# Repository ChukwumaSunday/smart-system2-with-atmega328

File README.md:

# smart-system2-with-atmega328
Pro-Tracking Solution Board is an ecosystem friendly onboard tracking technology and multi-functional development board based on ATMEGA328 microcontroller, designed to meet the requirements of embedded systems, vehicles/general tracking, providing a comprehensive set of features and peripherals on a single chip. 

PRO TRACKER SYSTEM
ABSTRACT:
The research is about creating a system for tracking vehicle, driver and products. Objective of the research is to design, develop and develop a GPS based
Tracking System in order to monitor and display location of vehicle on Google Maps and Other Dashboards. This system used ATMEGA328 as a microcontroller and it will be used as the main processing unit. Next, SIM7600E 4G LTE GSM/GPS module is used for network connectivity, routing the coordinate and connecting with the user.

INTRODUCTION
	Pro-Tracker Solution Board is an ecosystem friendly onboard tracking technology and multi-functional development board based on SIM7600E module that supports 4G network and  also support 2G/3G network communications, controlled by STM32 microcontroller, designed to meet the requirements of embedded systems, vehicles/general tracking, providing a comprehensive set of features and peripherals on a single board for DIY project kits. 
	The system is optimized for low power consumption and real-time processing, making it suitable for wide rand of applications.

AIM:
	To develop a multi-fuctional system that will solve the problem of location, driver and product tracking for both the military and civilians, perform driver and vehicle control, real time monitoring and ubiquitous in developing embedded systems/IoT technologies.
	To optimize the system for low power consumption and real-time processing, making it suitable for wide rand of applications.
	  To design a system that can be used in consumer products such as Vehicle Tracking System(VTS), Appliances Remote Controls, Motor Control Systems, IoT Projects, Medical devices, Gaming Console, Home Automation Systems and more.
Achievement: 
	Done with the schematic designs, board layout and ready for PCB fabrication.
Result: 
	No test carried out yet on the system as it’s still at design stage
Status of the project: 
	First stage which is PCB development is done. Therefore, the project is 40% near completion.
Conclusion:
	 All hands are on desk to ensure the project is completed as soon as possible if all the necessary system requirements are made available.

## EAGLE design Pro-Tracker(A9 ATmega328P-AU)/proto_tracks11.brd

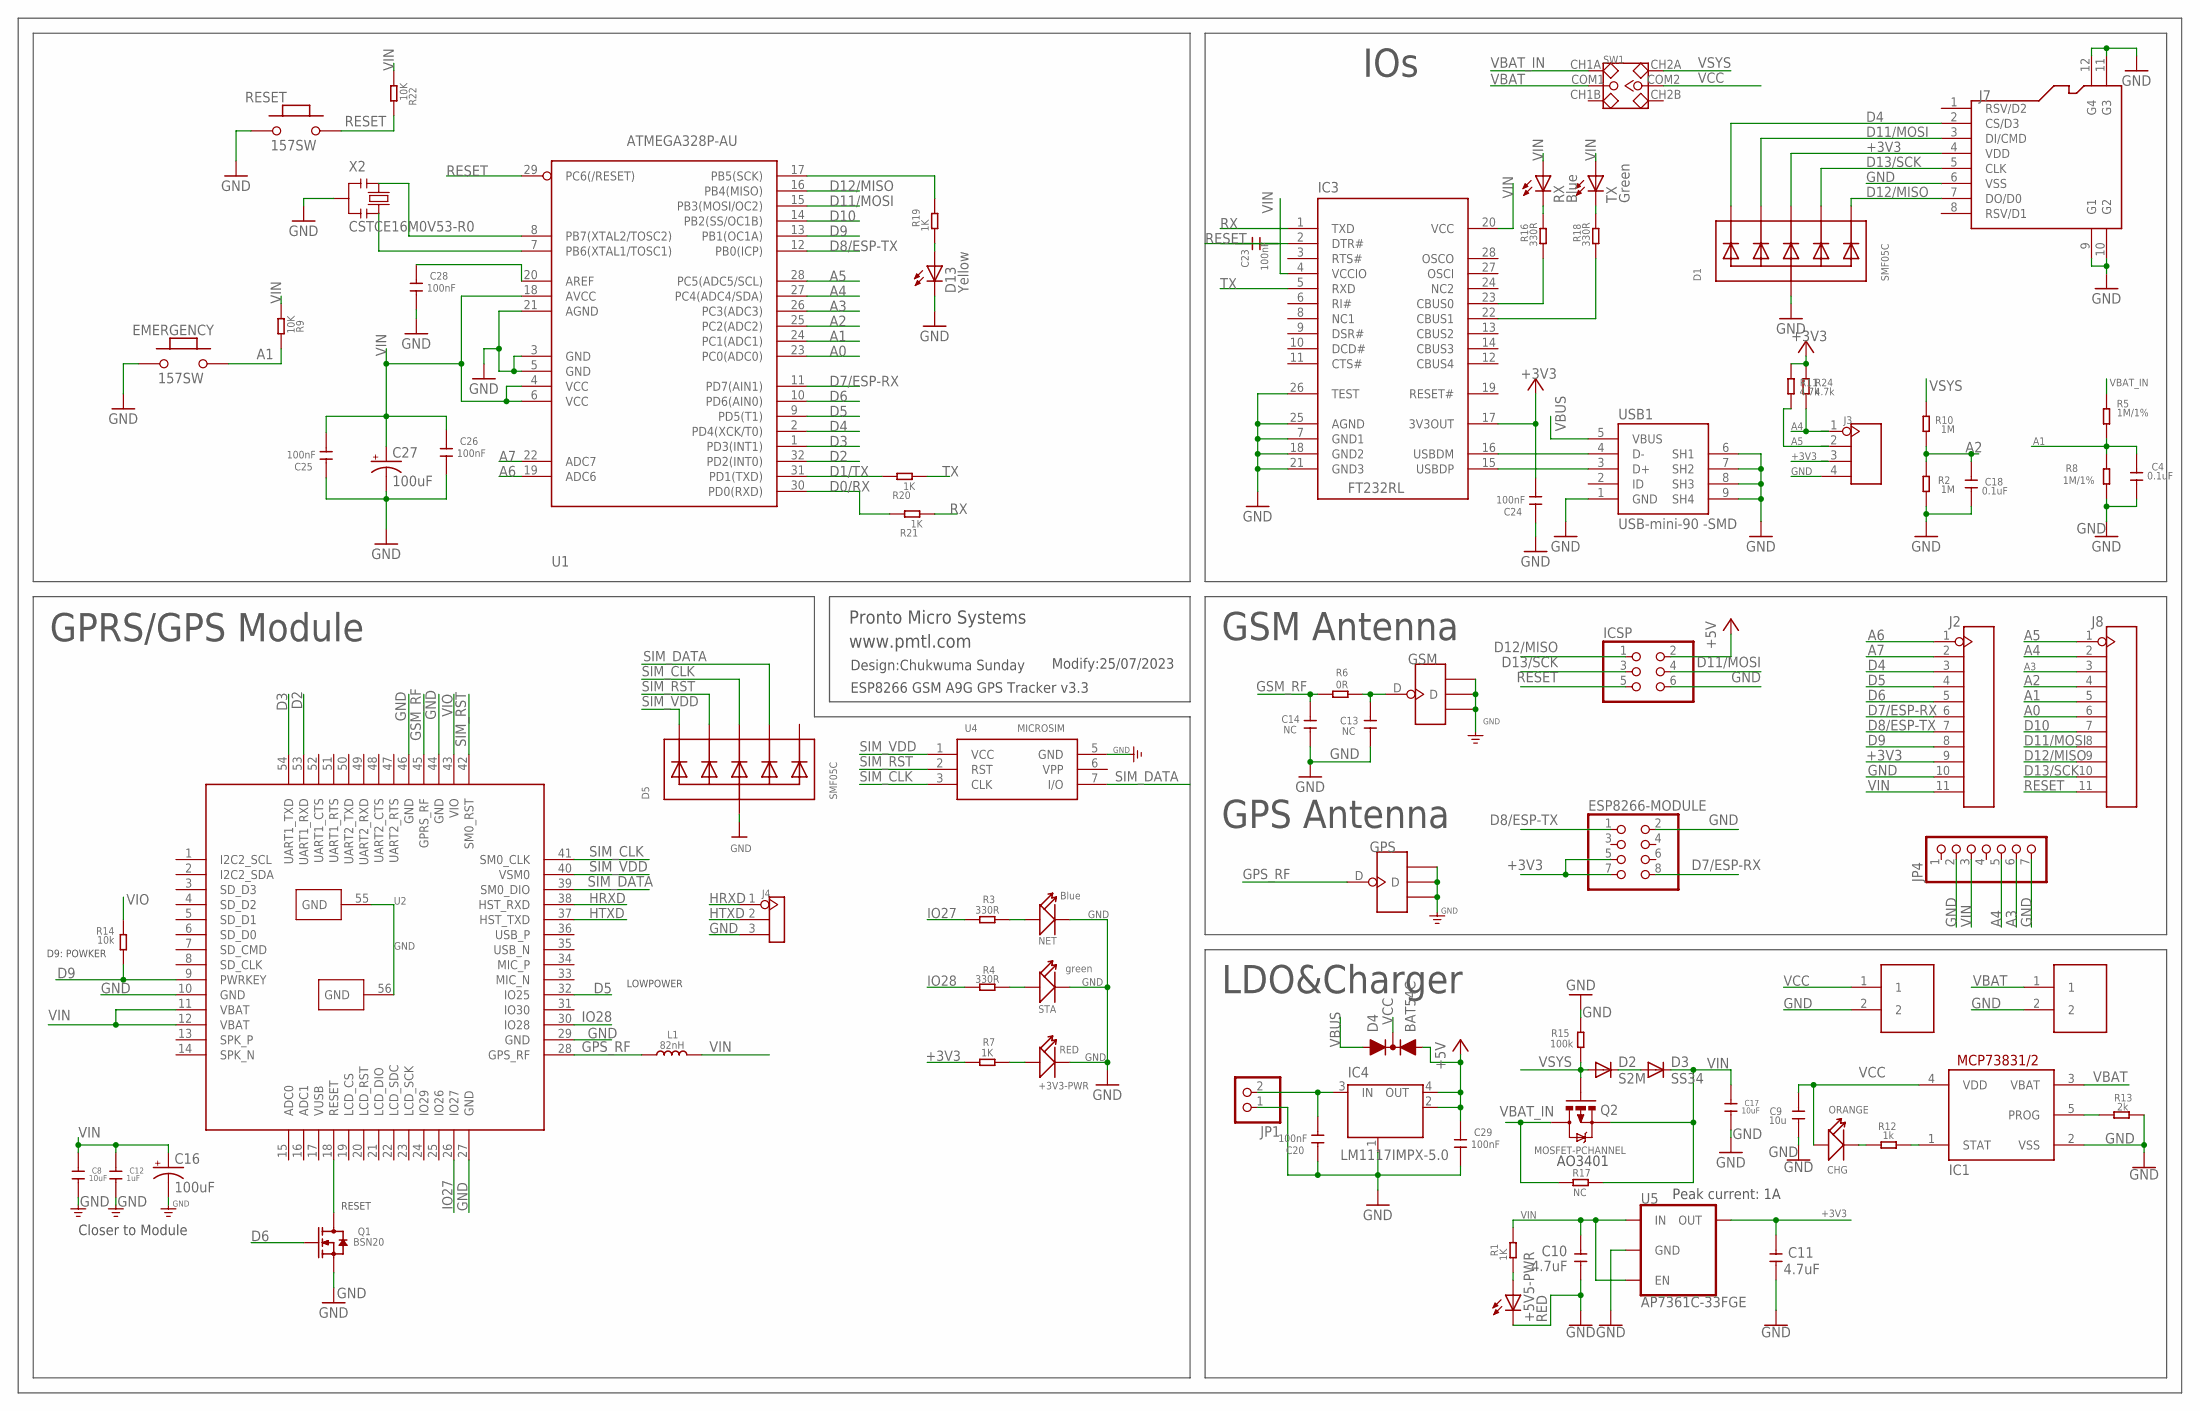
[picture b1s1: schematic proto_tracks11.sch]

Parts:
+3V3-PWR: RED; LED-0603
+5V5-PWR: RED; OPTO_CHIPLED_0805
C4, C18: 0.1uF; C0603
C8, C17: 10uF; C0603
C9: 10u; C0603
C10, C11: 4.7uF; C0603
C12: 1uF; C0603
C13, C14: NC; C0402
C16, C27: 100uF; EIA3528
C20, C23, C24, C25, C26, C28, C29: 100nF; C0603
CHG: ORANGE; D0603
D1, D5: SMF05C; SOT363
D2: S2M; DO-214AC
D3: SS34; DO-214AC
D4: BAT54C; SOT23-R
D13: Yellow; OPTO_CHIPLED_0805
EMERGENCY: 157SW; SWITCHES_SMD_157SW
ESP8266-MODULE: PINHD-2X4; 2X04
GPS: ANTENNA-U-FL; 4P-U-FL
GSM: ANTENNA-U-FL; 4P-U-FL
IC1: MCP73831/OT; SOT23-5L
IC3: FT232RL; INTEGRATEDCIRCUITS_SSOP28
IC4: LM1117IMPX-5.0; INTEGRATEDCIRCUITS_LINEAR_SOT223
ICSP: PINHD-2X3; 2X03
J1, J6: PH2.0-2P-90-DIP
J2, J8: HEADER-11P-2.54; 11P-2.54
J3: HEADER-4P-60/35MILROUND; 4P-65/35ROUND
J4: HEADER-3P-2.54; 3P-2.54
J7: HOLDER-MICROSD-8P; 8P-SMD
JP1: PINHD-1X2; 1X02
JP4: PINHD-1X7; 1X07
L1: 82nH; L0603
NET: Blue; LED-0603
Q1: BSN20; SOT23@1
Q2: MOSFET-PCHANNEL; SOT23-3
R1, R7, R19, R20, R21: 1K; R0603
R2, R10: 1M; R0603
R3, R4, R16, R18: 330R; R0603
R5, R8: 1M/1%; R0603
R6: 0R; R0603
R9, R22: 10K; R0603
R11, R24: 4.7k; R0603
R12: 1k; R0603
R13: 2k; R0603
R14: 10k; R0603
R15: 100k; R0603
R17: NC; R0603
RESET: 157SW; SWITCHES_SMD_157SW
RX: Blue; OPTO_CHIPLED_0805
STA: green; LED-0603
SW1: SWITCH-2CH-6P; 6P-2CH-2.54-7.6X3.0
TX: Green; OPTO_CHIPLED_0805
U1: ATMEGA328P-AU; ARDUINO-UCS&SOCS_TQFP32-08
U2: A9G
U4: MICROSIM
U5: AP7361C-33FGE; 8-UDFN
USB1: USB-mini-90 -SMD; CONNETTORI_USB-MINI-B_2
X2: CSTCE16M0V53-R0; CRISTALLI_RESONATOR

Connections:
+3V3: C11.2, C24.2, D1.4 (C3), ESP8266-MODULE.5, ESP8266-MODULE.7, IC3.17 (3V3OUT), J2.9, J3.3, J7.4 (VDD), R7.1, R11.2, R24.2, U5.1 (OUT)
+5V: C29.1, D4.2 (A2), IC4.2 (OUT), IC4.4 (OUT), ICSP.2
A0: J8.6, U1.23 (PC0(ADC0))
A1: C4.1, EMERGENCY.2, J8.5, R5.1, R8.2, R9.2, U1.24 (PC1(ADC1))
A2: C18.1, J8.4, R2.2, R10.1, U1.25 (PC2(ADC2))
A3: J8.3, JP4.6, U1.26 (PC3(ADC3))
A4: J3.1, J8.2, JP4.5, R24.1, U1.27 (PC4(ADC4/SDA))
A5: J3.2, J8.1, R11.1, U1.28 (PC5(ADC5/SCL))
A6: J2.1, U1.19 (ADC6)
A7: J2.2, U1.22 (ADC7)
D0/RX: R21.2, U1.30 (PD0(RXD))
D1/TX: R20.2, U1.31 (PD1(TXD))
D2: U1.32 (PD2(INT0)), U2.53 (UART1_RXD)
D3: U1.1 (PD3(INT1)), U2.54 (UART1_TXD)
D4: D1.1 (C1), J2.3, J7.2 (CS/D3), U1.2 (PD4(XCK/T0))
D5: J2.4, U1.9 (PD5(T1)), U2.32 (IO25)
D6: J2.5, Q1.1 (G), U1.10 (PD6(AIN0))
D7/ESP-RX: ESP8266-MODULE.8, J2.6, U1.11 (PD7(AIN1))
D8/ESP-TX: ESP8266-MODULE.1, J2.7, U1.12 (PB0(ICP))
D9: J2.8, R14.1, U1.13 (PB1(OC1A)), U2.9 (PWRKEY)
D10: J8.7, U1.14 (PB2(SS/OC1B))
D11/MOSI: D1.3 (C2), ICSP.4, J7.3 (DI/CMD), J8.8, U1.15 (PB3(MOSI/OC2))
D12/MISO: D1.6 (C5), ICSP.1, J7.7 (DO/D0), J8.9, U1.16 (PB4(MISO))
D13/SCK: D1.5 (C4), ICSP.3, J7.5 (CLK), J8.10, R19.2, U1.17 (PB5(SCK))
GND: +3V3-PWR.-, +5V5-PWR.C, C4.2, C8.1, C9.1, C10.1, C11.1, C12.1, C13.1, C14.1, C16.C (-), C17.1, C18.2, C20.1, C24.1, C25.1, C26.2, C27.C (-), C28.2, C29.2, D1.2 (A), D5.2 (A), D13.C, EMERGENCY.1, ESP8266-MODULE.2, GPS.GND1, GPS.GND2, GPS.GND3, GSM.GND1, GSM.GND2, GSM.GND3, IC1.2 (VSS), IC3.7 (GND1), IC3.18 (GND2), IC3.21 (GND3), IC3.25 (AGND), IC3.26 (TEST), IC4.1 (GND/ADJ), ICSP.6, J1.2, J2.10, J3.4, J4.3, J6.2, J7.6 (VSS), J7.9 (G1), J7.10 (G2), J7.11 (G3), J7.12 (G4), JP1.1, JP4.2, JP4.7, NET.-, Q1.2 (S), R2.1, R8.1, R13.2, R15.2, RESET.1, STA.-, U1.3 (GND), U1.5 (GND), U1.21 (AGND), U2.10 (GND), U2.27 (GND), U2.29 (GND), U2.44 (GND), U2.46 (GND), U2.55 (GND), U2.56 (GND), U4.5 (GND), U5.4 (GND), U5.EP (GND), USB1.1 (GND), USB1.6 (SH1), USB1.7 (SH2), USB1.8 (SH3), USB1.9 (SH4), X2.2
GPS_RF: GPS.D, L1.1, U2.28 (GPS_RF)
GSM_RF: C14.2, R6.1, U2.45 (GPRS_RF)
HRXD: J4.1, U2.38 (HST_RXD)
HTXD: J4.2, U2.37 (HST_TXD)
IO27: R3.1, U2.26 (IO27)
IO28: R4.1, U2.30 (IO28)
unnamed: R4.2, STA.+
unnamed: D2.C, D3.A
unnamed: +3V3-PWR.+, R7.2
unnamed: C28.1, U1.20 (AREF)
unnamed: +5V5-PWR.A, R1.1
unnamed: C20.2, IC4.3 (IN), JP1.2
unnamed: NET.+, R3.2
unnamed: Q1.3 (D), U2.18 (RESET)
unnamed: C23.2, IC3.2 (DTR#)
unnamed: R16.2, RX.C
unnamed: R18.2, TX.C
unnamed: IC3.23 (CBUS0), R16.1
unnamed: IC3.22 (CBUS1), R18.1
unnamed: IC3.15 (USBDP), USB1.3 (D+)
unnamed: IC3.16 (USBDM), USB1.4 (D-)
unnamed: D13.A, R19.1
unnamed: CHG.-, R12.1
unnamed: IC1.1 (STAT), R12.2
unnamed: IC1.5 (PROG), R13.1
unnamed: U1.7 (PB6(XTAL1/TOSC1)), X2.3
unnamed: U1.8 (PB7(XTAL2/TOSC2)), X2.1
unnamed: C13.2, GSM.D, R6.2
RESET: C23.1, ICSP.5, J8.11, R22.2, RESET.2, U1.29 (PC6(/RESET))
RX: IC3.1 (TXD), R21.1
SIM_CLK: D5.4 (C3), U2.41 (SM0_CLK), U4.3 (CLK)
SIM_DATA: D5.5 (C4), U2.39 (SM0_DIO), U4.7 (I/O)
SIM_RST: D5.3 (C2), U2.42 (SM0_RST), U4.2 (RST)
SIM_VDD: D5.1 (C1), U2.40 (VSM0), U4.1 (VCC)
TX: IC3.5 (RXD), R20.1
VBAT: IC1.3 (VBAT), J6.1, SW1.COM1
VBAT_IN: Q2.3 (D), R5.2, R17.1, SW1.CH1A
VBUS: D4.1 (A1), USB1.5 (VBUS)
VCC: C9.2, CHG.+, D4.3 (C), IC1.4 (VDD), J1.1, SW1.COM2
VIN: C8.2, C10.2, C12.2, C16.A (+), C17.2, C25.2, C26.1, C27.A (+), D3.C, IC3.4 (VCCIO), IC3.20 (VCC), J2.11, JP4.3, L1.2, Q2.2 (S), R1.2, R9.1, R17.2, R22.1, RX.A, TX.A, U1.4 (VCC), U1.6 (VCC), U1.18 (AVCC), U2.11 (VBAT), U2.12 (VBAT), U5.5 (EN), U5.8 (IN)
VIO: R14.2, U2.43 (VIO)
VSYS: D2.A, Q2.1 (G), R10.2, R15.1, SW1.CH2A

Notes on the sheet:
GSM Antenna
GPRS/GPS Module
LOWPOWER
RESET
D9: POWKER
Peak current: 1A
www.pmtl.com
IOs
LDO&Charger
GPS Antenna
Design:Chukwuma Sunday
Modify:25/07/2023
Pronto Micro Systems
Closer to Module
AO3401
ESP8266 GSM A9G GPS Tracker v3.3

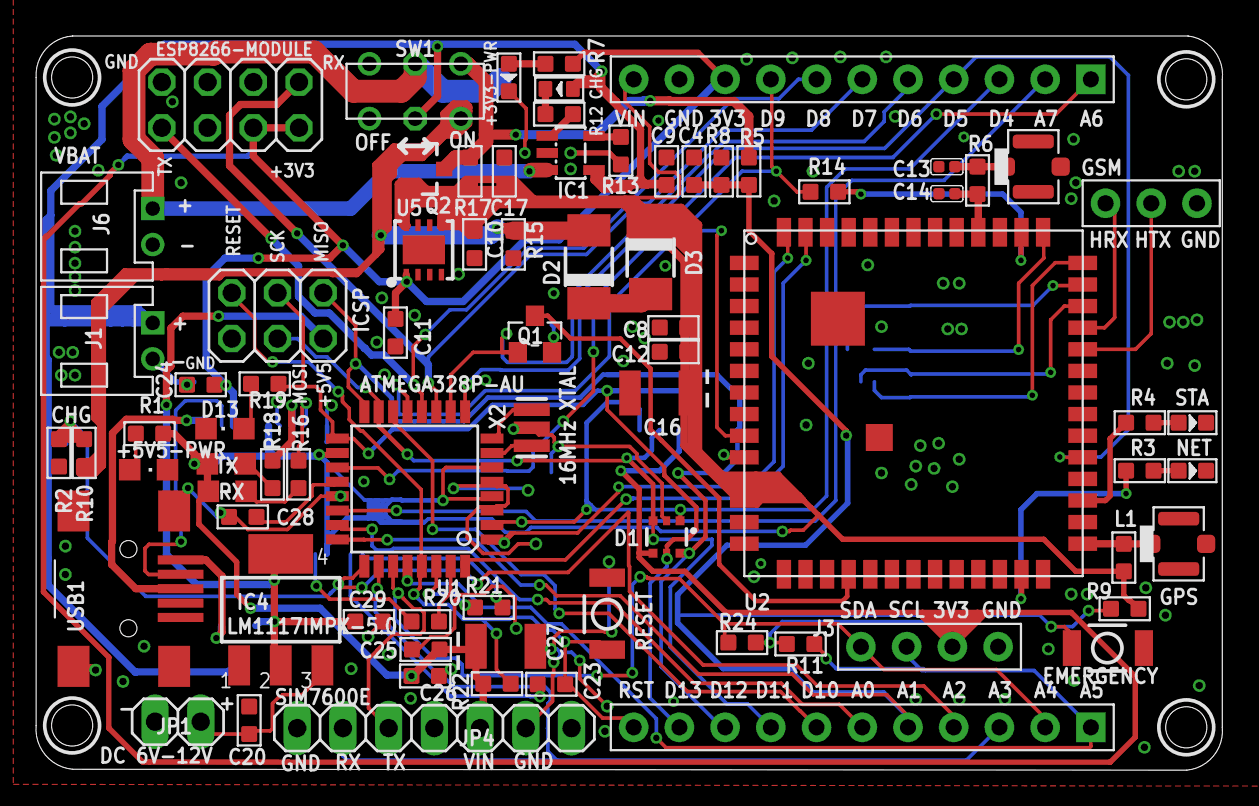
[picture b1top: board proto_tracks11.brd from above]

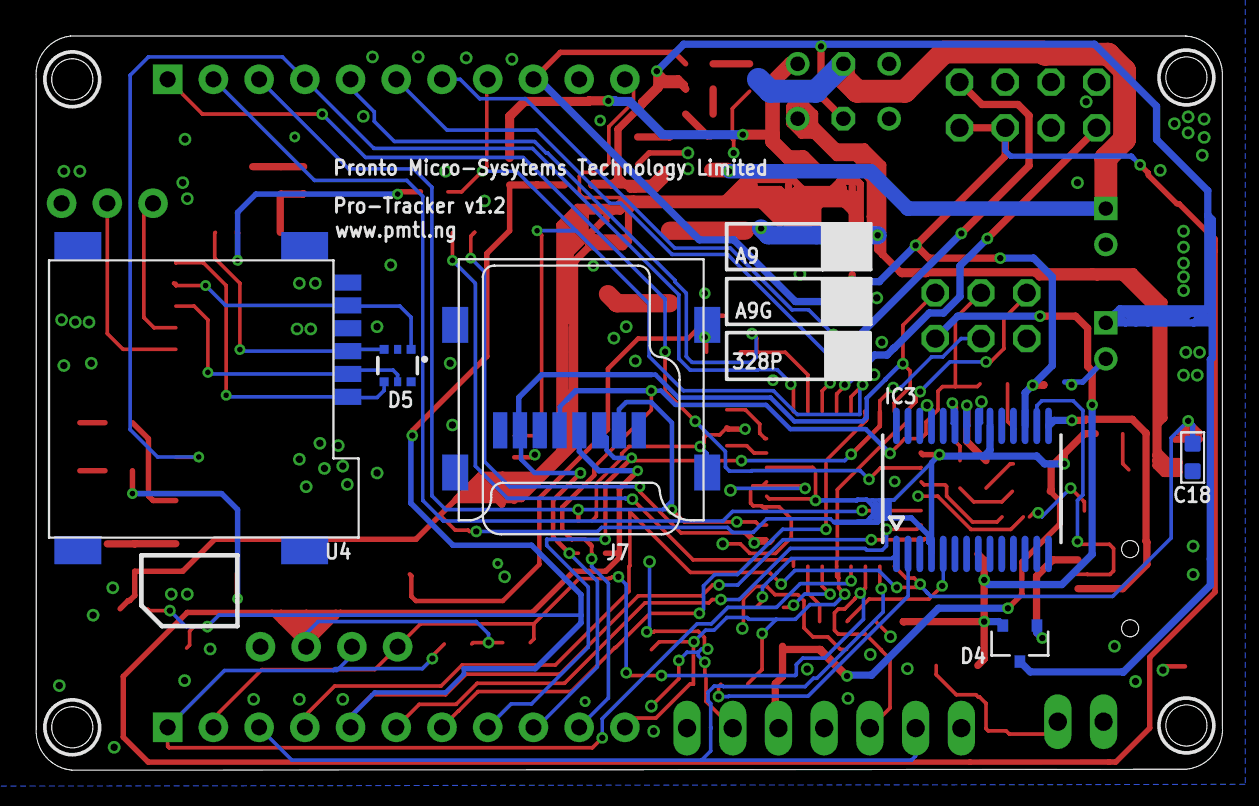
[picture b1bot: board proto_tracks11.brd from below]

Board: 2 copper layers, 65.9 x 40.8 mm, 83 parts (6 on the bottom side), 67 nets.

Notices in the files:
parts and their libraries:
microbuilder: This work is placed in the public domain, and may be freely used for commercial and non-commercial work with the following conditions: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
SparkFun-Capacitors: Licensing: Creative Commons ShareAlike 4.0 International - https://creativecommons.org/licenses/by-sa/4.0
